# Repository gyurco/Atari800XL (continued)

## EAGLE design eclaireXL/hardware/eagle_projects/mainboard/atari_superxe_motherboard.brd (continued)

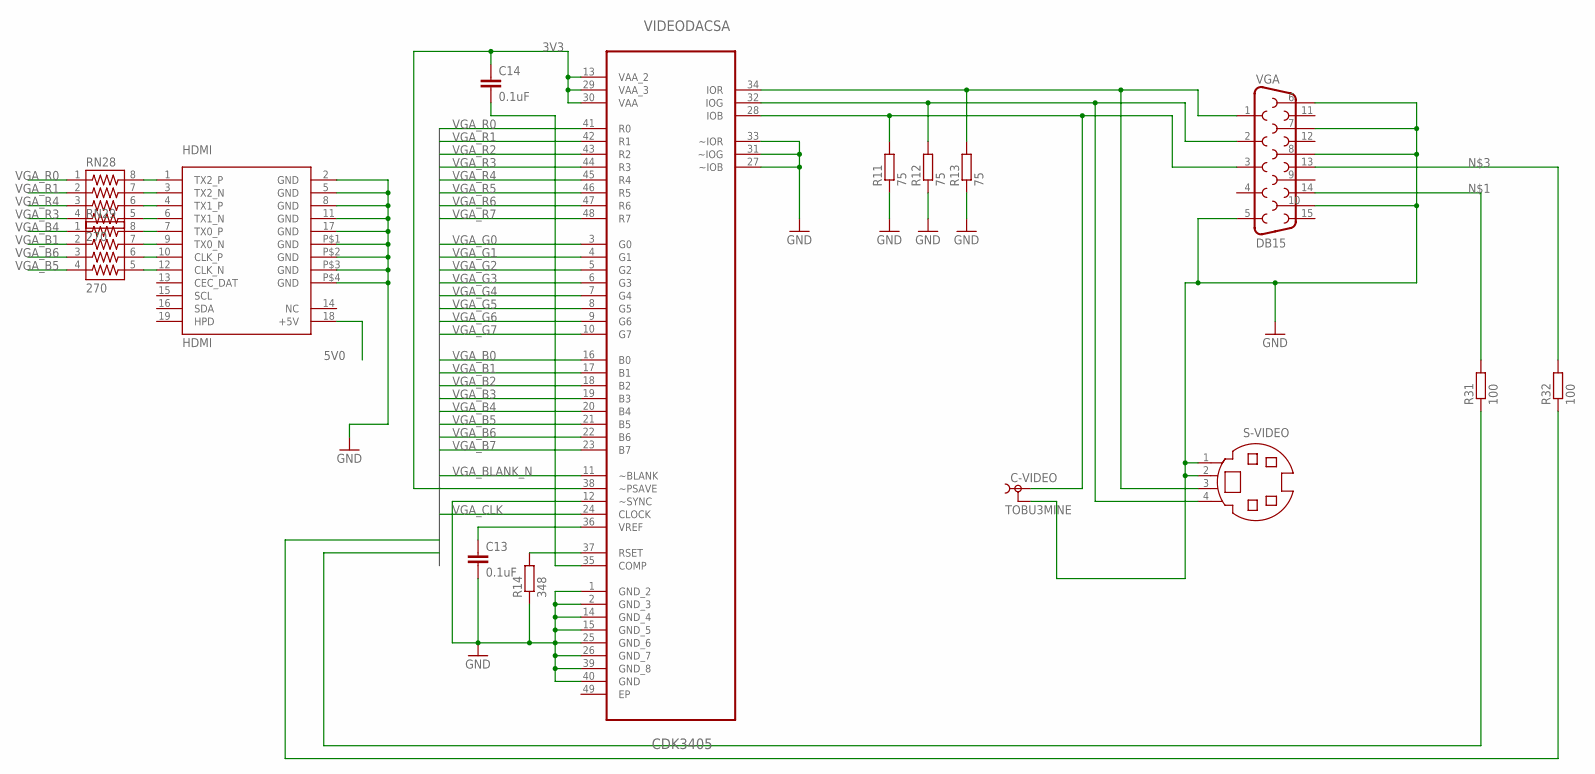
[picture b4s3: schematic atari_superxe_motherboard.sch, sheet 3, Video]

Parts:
C13, C14: 0.1uF; C0805
C-VIDEO: TOBU3MINE; TOBU3_EXT
HDMI: HDMI
R11, R12, R13: 75; M0805
R14: 348; M0805
R31, R32: 100; R0805
RN28, RN29: 270; 743-8
S-VIDEO: MD04SS; MDIN04SS
VGA: DB15
VIDEODACSA: CDK3405; QFP50P900X900X120-49N

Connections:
3V3: C14.1, VIDEODACSA.13 (VAA_2), VIDEODACSA.29 (VAA_3), VIDEODACSA.30 (VAA), VIDEODACSA.38 (~PSAVE); also elsewhere on the board
5V0: HDMI.18 (+5V); also elsewhere on the board
GND: C13.2, C-VIDEO.2, C-VIDEO.2@1 (2), C-VIDEO.2@2 (2), HDMI.2 (GND), HDMI.5 (GND), HDMI.8 (GND), HDMI.11 (GND), HDMI.17 (GND), HDMI.P$1 (GND), HDMI.P$2 (GND), HDMI.P$3 (GND), HDMI.P$4 (GND), R11.1, R12.1, R13.1, R14.1, S-VIDEO.1, S-VIDEO.2, VGA.5, VGA.6, VGA.7, VGA.8, VGA.10, VIDEODACSA.1 (GND_2), VIDEODACSA.2 (GND_3), VIDEODACSA.12 (~SYNC), VIDEODACSA.14 (GND_4), VIDEODACSA.15 (GND_5), VIDEODACSA.25 (GND_6), VIDEODACSA.26 (GND_7), VIDEODACSA.27 (~IOB), VIDEODACSA.31 (~IOG), VIDEODACSA.33 (~IOR), VIDEODACSA.39 (GND_8), VIDEODACSA.40 (GND); also elsewhere on the board
HSYNC: R32.1; also elsewhere on the board
unnamed: R31.2, VGA.14
unnamed: R32.2, VGA.13
unnamed: R13.2, S-VIDEO.3, VGA.1, VIDEODACSA.34 (IOR)
unnamed: R12.2, S-VIDEO.4, VGA.2, VIDEODACSA.32 (IOG)
unnamed: C13.1, VIDEODACSA.36 (VREF)
unnamed: R14.2, VIDEODACSA.37 (RSET)
unnamed: C14.2, VIDEODACSA.35 (COMP)
unnamed: HDMI.1 (TX2_P), RN28.8
unnamed: C-VIDEO.1, R11.2, VGA.3, VIDEODACSA.28 (IOB)
unnamed: HDMI.3 (TX2_N), RN28.7
unnamed: HDMI.4 (TX1_P), RN28.6
unnamed: HDMI.6 (TX1_N), RN28.5
unnamed: HDMI.7 (TX0_P), RN29.8
unnamed: HDMI.9 (TX0_N), RN29.7
unnamed: HDMI.10 (CLK_P), RN29.6
unnamed: HDMI.12 (CLK_N), RN29.5
VGA_B0: VIDEODACSA.16 (B0); also elsewhere on the board
VGA_B1: RN29.2, VIDEODACSA.17 (B1); also elsewhere on the board
VGA_B2: VIDEODACSA.18 (B2); also elsewhere on the board
VGA_B3: VIDEODACSA.19 (B3); also elsewhere on the board
VGA_B4: RN29.1, VIDEODACSA.20 (B4); also elsewhere on the board
VGA_B5: RN29.4, VIDEODACSA.21 (B5); also elsewhere on the board
VGA_B6: RN29.3, VIDEODACSA.22 (B6); also elsewhere on the board
VGA_B7: VIDEODACSA.23 (B7); also elsewhere on the board
VGA_BLANK_N: VIDEODACSA.11 (~BLANK); also elsewhere on the board
VGA_CLK: VIDEODACSA.24 (CLOCK); also elsewhere on the board
VGA_G0: VIDEODACSA.3 (G0); also elsewhere on the board
VGA_G1: VIDEODACSA.4 (G1); also elsewhere on the board
VGA_G2: VIDEODACSA.5 (G2); also elsewhere on the board
VGA_G3: VIDEODACSA.6 (G3); also elsewhere on the board
VGA_G4: VIDEODACSA.7 (G4); also elsewhere on the board
VGA_G5: VIDEODACSA.8 (G5); also elsewhere on the board
VGA_G6: VIDEODACSA.9 (G6); also elsewhere on the board
VGA_G7: VIDEODACSA.10 (G7); also elsewhere on the board
VGA_R0: RN28.1, VIDEODACSA.41 (R0); also elsewhere on the board
VGA_R1: RN28.2, VIDEODACSA.42 (R1); also elsewhere on the board
VGA_R2: VIDEODACSA.43 (R2); also elsewhere on the board
VGA_R3: RN28.4, VIDEODACSA.44 (R3); also elsewhere on the board
VGA_R4: RN28.3, VIDEODACSA.45 (R4); also elsewhere on the board
VGA_R5: VIDEODACSA.46 (R5); also elsewhere on the board
VGA_R6: VIDEODACSA.47 (R6); also elsewhere on the board
VGA_R7: VIDEODACSA.48 (R7); also elsewhere on the board
VSYNC: R31.1; also elsewhere on the board

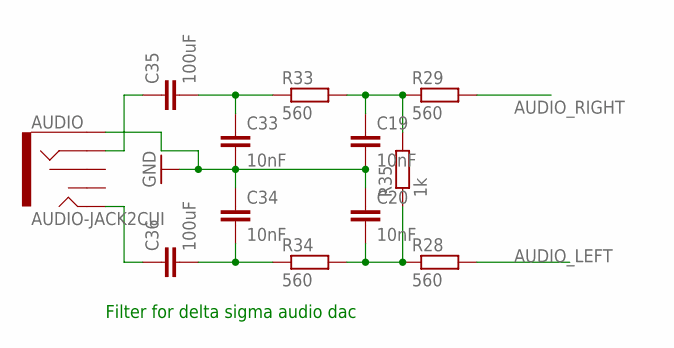
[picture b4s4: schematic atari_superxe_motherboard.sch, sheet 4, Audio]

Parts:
AUDIO: AUDIO-JACK2CUI; AUDIO-JACK-CUI-353X
C19, C20, C33, C34: 10nF; C0805
C35, C36: 100uF; C1206
R28, R29, R33, R34: 560; M0805
R35: 1k; M0805

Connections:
AUDIO_LEFT: R28.2; also elsewhere on the board
AUDIO_RIGHT: R29.2; also elsewhere on the board
GND: AUDIO.P$1 (SLEEVE), C19.2, C20.1, C33.2, C34.1; also elsewhere on the board
unnamed: C33.1, C35.2, R33.1
unnamed: C19.1, R29.1, R33.2, R35.2
unnamed: C20.2, R28.1, R34.2, R35.1
unnamed: AUDIO.P$3 (RING), C35.1
unnamed: AUDIO.P$2 (TIP), C36.1
unnamed: C34.2, C36.2, R34.1

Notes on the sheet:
Filter for delta sigma audio dac

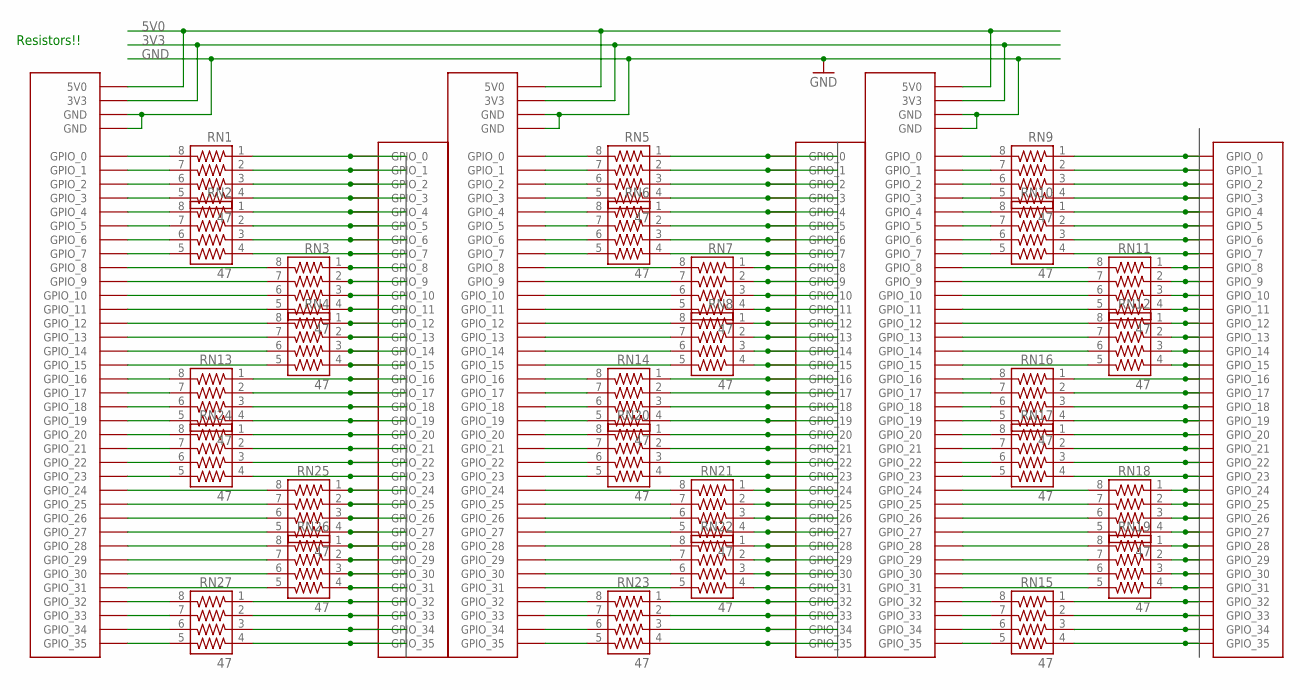
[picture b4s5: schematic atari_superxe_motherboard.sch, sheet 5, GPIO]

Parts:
GPIO_A: DE1_GPIO; DIL-100-2X20
GPIO_B: DE1_GPIO; DIL-100-2X20
GPIO_C: DE1_GPIO; DIL-100-2X20
RN1, RN2, RN3, RN4, RN5, RN6, RN7, RN8, RN9, RN10, RN11, RN12, RN13, RN14, RN15, RN16, RN17, RN18, RN19, RN20, RN21, RN22, RN23, RN24, RN25, RN26, RN27: 47; 743-8
U$3, U$4, U$5: HDR_SMALL_36_DEV_LALIGNED; HDR_141_36

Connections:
3V3: GPIO_A.29 (3V3), GPIO_B.29 (3V3), GPIO_C.29 (3V3); also elsewhere on the board
5V0: GPIO_A.11 (5V0), GPIO_B.11 (5V0), GPIO_C.11 (5V0); also elsewhere on the board
GND: GPIO_A.12 (GND), GPIO_A.30 (GND), GPIO_B.12 (GND), GPIO_B.30 (GND), GPIO_C.12 (GND), GPIO_C.30 (GND); also elsewhere on the board
GPIOA0: RN1.1, U$5.P$1 (GPIO_0); also elsewhere on the board
GPIOA1: RN1.2, U$5.P$2 (GPIO_1); also elsewhere on the board
GPIOA2: RN1.3, U$5.P$3 (GPIO_2); also elsewhere on the board
GPIOA3: RN1.4, U$5.P$4 (GPIO_3); also elsewhere on the board
GPIOA4: RN2.1, U$5.P$5 (GPIO_4); also elsewhere on the board
GPIOA5: RN2.2, U$5.P$6 (GPIO_5); also elsewhere on the board
GPIOA6: RN2.3, U$5.P$7 (GPIO_6); also elsewhere on the board
GPIOA7: RN2.4, U$5.P$8 (GPIO_7); also elsewhere on the board
GPIOA8: RN3.1, U$5.P$9 (GPIO_8); also elsewhere on the board
GPIOA9: RN3.2, U$5.P$10 (GPIO_9); also elsewhere on the board
GPIOA10: RN3.3, U$5.P$11 (GPIO_10); also elsewhere on the board
GPIOA11: RN3.4, U$5.P$12 (GPIO_11); also elsewhere on the board
GPIOA12: RN4.1, U$5.P$13 (GPIO_12); also elsewhere on the board
GPIOA13: RN4.2, U$5.P$14 (GPIO_13); also elsewhere on the board
GPIOA14: RN4.3, U$5.P$15 (GPIO_14); also elsewhere on the board
GPIOA15: RN4.4, U$5.P$16 (GPIO_15); also elsewhere on the board
GPIOA16: RN13.1, U$5.P$17 (GPIO_16); also elsewhere on the board
GPIOA17: RN13.2, U$5.P$18 (GPIO_17); also elsewhere on the board
GPIOA18: RN13.3, U$5.P$19 (GPIO_18); also elsewhere on the board
GPIOA19: RN13.4, U$5.P$20 (GPIO_19); also elsewhere on the board
GPIOA20: RN24.1, U$5.P$21 (GPIO_20); also elsewhere on the board
GPIOA21: RN24.2, U$5.P$22 (GPIO_21); also elsewhere on the board
GPIOA22: RN24.3, U$5.P$23 (GPIO_22); also elsewhere on the board
GPIOA23: RN24.4, U$5.P$24 (GPIO_23); also elsewhere on the board
GPIOA24: RN25.1, U$5.P$25 (GPIO_24); also elsewhere on the board
GPIOA25: RN25.2, U$5.P$26 (GPIO_25); also elsewhere on the board
GPIOA26: RN25.3, U$5.P$27 (GPIO_26); also elsewhere on the board
GPIOA27: RN25.4, U$5.P$28 (GPIO_27); also elsewhere on the board
GPIOA28: RN26.1, U$5.P$29 (GPIO_28); also elsewhere on the board
GPIOA29: RN26.2, U$5.P$30 (GPIO_29); also elsewhere on the board
GPIOA30: RN26.3, U$5.P$31 (GPIO_30); also elsewhere on the board
GPIOA31: RN26.4, U$5.P$32 (GPIO_31); also elsewhere on the board
GPIOA32: RN27.1, U$5.P$33 (GPIO_32); also elsewhere on the board
GPIOA33: RN27.2, U$5.P$34 (GPIO_33); also elsewhere on the board
GPIOA34: RN27.3, U$5.P$35 (GPIO_34); also elsewhere on the board
GPIOA35: RN27.4, U$5.P$36 (GPIO_35); also elsewhere on the board
GPIOB0: RN5.1, U$4.P$1 (GPIO_0); also elsewhere on the board
GPIOB1: RN5.2, U$4.P$2 (GPIO_1); also elsewhere on the board
GPIOB2: RN5.3, U$4.P$3 (GPIO_2); also elsewhere on the board
GPIOB3: RN5.4, U$4.P$4 (GPIO_3); also elsewhere on the board
GPIOB4: RN6.1, U$4.P$5 (GPIO_4); also elsewhere on the board
GPIOB5: RN6.2, U$4.P$6 (GPIO_5); also elsewhere on the board
GPIOB6: RN6.3, U$4.P$7 (GPIO_6); also elsewhere on the board
GPIOB7: RN6.4, U$4.P$8 (GPIO_7); also elsewhere on the board
GPIOB8: RN7.1, U$4.P$9 (GPIO_8); also elsewhere on the board
GPIOB9: RN7.2, U$4.P$10 (GPIO_9); also elsewhere on the board
GPIOB10: RN7.3, U$4.P$11 (GPIO_10); also elsewhere on the board
GPIOB11: RN7.4, U$4.P$12 (GPIO_11); also elsewhere on the board
GPIOB12: RN8.1, U$4.P$13 (GPIO_12); also elsewhere on the board
GPIOB13: RN8.2, U$4.P$14 (GPIO_13); also elsewhere on the board
GPIOB14: RN8.3, U$4.P$15 (GPIO_14); also elsewhere on the board
GPIOB15: RN8.4, U$4.P$16 (GPIO_15); also elsewhere on the board
GPIOB16: RN14.1, U$4.P$17 (GPIO_16); also elsewhere on the board
GPIOB17: RN14.2, U$4.P$18 (GPIO_17); also elsewhere on the board
GPIOB18: RN14.3, U$4.P$19 (GPIO_18); also elsewhere on the board
GPIOB19: RN14.4, U$4.P$20 (GPIO_19); also elsewhere on the board
GPIOB20: RN20.1, U$4.P$21 (GPIO_20); also elsewhere on the board
GPIOB21: RN20.2, U$4.P$22 (GPIO_21); also elsewhere on the board
GPIOB22: RN20.3, U$4.P$23 (GPIO_22); also elsewhere on the board
GPIOB23: RN20.4, U$4.P$24 (GPIO_23); also elsewhere on the board
GPIOB24: RN21.1, U$4.P$25 (GPIO_24); also elsewhere on the board
GPIOB25: RN21.2, U$4.P$26 (GPIO_25); also elsewhere on the board
GPIOB26: RN21.3, U$4.P$27 (GPIO_26); also elsewhere on the board
GPIOB27: RN21.4, U$4.P$28 (GPIO_27); also elsewhere on the board
GPIOB28: RN22.1, U$4.P$29 (GPIO_28); also elsewhere on the board
GPIOB29: RN22.2, U$4.P$30 (GPIO_29); also elsewhere on the board
GPIOB30: RN22.3, U$4.P$31 (GPIO_30); also elsewhere on the board
GPIOB31: RN22.4, U$4.P$32 (GPIO_31); also elsewhere on the board
GPIOB32: RN23.1, U$4.P$33 (GPIO_32); also elsewhere on the board
GPIOB33: RN23.2, U$4.P$34 (GPIO_33); also elsewhere on the board
GPIOB34: RN23.3, U$4.P$35 (GPIO_34); also elsewhere on the board
GPIOB35: RN23.4, U$4.P$36 (GPIO_35); also elsewhere on the board
GPIOC0: RN9.1, U$3.P$1 (GPIO_0); also elsewhere on the board
GPIOC1: RN9.2, U$3.P$2 (GPIO_1); also elsewhere on the board
GPIOC2: RN9.3, U$3.P$3 (GPIO_2); also elsewhere on the board
GPIOC3: RN9.4, U$3.P$4 (GPIO_3); also elsewhere on the board
GPIOC4: RN10.1, U$3.P$5 (GPIO_4); also elsewhere on the board
GPIOC5: RN10.2, U$3.P$6 (GPIO_5); also elsewhere on the board
GPIOC6: RN10.3, U$3.P$7 (GPIO_6); also elsewhere on the board
GPIOC7: RN10.4, U$3.P$8 (GPIO_7); also elsewhere on the board
GPIOC8: RN11.1, U$3.P$9 (GPIO_8); also elsewhere on the board
GPIOC9: RN11.2, U$3.P$10 (GPIO_9); also elsewhere on the board
GPIOC10: RN11.3, U$3.P$11 (GPIO_10); also elsewhere on the board
GPIOC11: RN11.4, U$3.P$12 (GPIO_11); also elsewhere on the board
GPIOC12: RN12.1, U$3.P$13 (GPIO_12); also elsewhere on the board
GPIOC13: RN12.2, U$3.P$14 (GPIO_13); also elsewhere on the board
GPIOC14: RN12.3, U$3.P$15 (GPIO_14); also elsewhere on the board
GPIOC15: RN12.4, U$3.P$16 (GPIO_15); also elsewhere on the board
GPIOC16: RN16.1, U$3.P$17 (GPIO_16); also elsewhere on the board
GPIOC17: RN16.2, U$3.P$18 (GPIO_17); also elsewhere on the board
GPIOC18: RN16.3, U$3.P$19 (GPIO_18); also elsewhere on the board
GPIOC19: RN16.4, U$3.P$20 (GPIO_19); also elsewhere on the board
GPIOC20: RN17.1, U$3.P$21 (GPIO_20); also elsewhere on the board
GPIOC21: RN17.2, U$3.P$22 (GPIO_21); also elsewhere on the board
GPIOC22: RN17.3, U$3.P$23 (GPIO_22); also elsewhere on the board
GPIOC23: RN17.4, U$3.P$24 (GPIO_23); also elsewhere on the board
GPIOC24: RN18.1, U$3.P$25 (GPIO_24); also elsewhere on the board
GPIOC25: RN18.2, U$3.P$26 (GPIO_25); also elsewhere on the board
GPIOC26: RN18.3, U$3.P$27 (GPIO_26); also elsewhere on the board
GPIOC27: RN18.4, U$3.P$28 (GPIO_27); also elsewhere on the board
GPIOC28: RN19.1, U$3.P$29 (GPIO_28); also elsewhere on the board
GPIOC29: RN19.2, U$3.P$30 (GPIO_29); also elsewhere on the board
GPIOC30: RN19.3, U$3.P$31 (GPIO_30); also elsewhere on the board
GPIOC31: RN19.4, U$3.P$32 (GPIO_31); also elsewhere on the board
GPIOC32: RN15.1, U$3.P$33 (GPIO_32); also elsewhere on the board
GPIOC33: RN15.2, U$3.P$34 (GPIO_33); also elsewhere on the board
GPIOC34: RN15.3, U$3.P$35 (GPIO_34); also elsewhere on the board
GPIOC35: RN15.4, U$3.P$36 (GPIO_35); also elsewhere on the board
unnamed: GPIO_C.1 (GPIO_0), RN9.8
unnamed: GPIO_A.1 (GPIO_0), RN1.8
unnamed: GPIO_A.2 (GPIO_1), RN1.7
unnamed: GPIO_A.3 (GPIO_2), RN1.6
unnamed: GPIO_A.4 (GPIO_3), RN1.5
unnamed: GPIO_A.5 (GPIO_4), RN2.8
unnamed: GPIO_A.6 (GPIO_5), RN2.7
unnamed: GPIO_A.7 (GPIO_6), RN2.6
unnamed: GPIO_A.8 (GPIO_7), RN2.5
unnamed: GPIO_A.9 (GPIO_8), RN3.8
unnamed: GPIO_A.10 (GPIO_9), RN3.7
unnamed: GPIO_A.13 (GPIO_10), RN3.6
unnamed: GPIO_A.14 (GPIO_11), RN3.5
unnamed: GPIO_A.15 (GPIO_12), RN4.8
unnamed: GPIO_A.17 (GPIO_14), RN4.6
unnamed: GPIO_A.16 (GPIO_13), RN4.7
unnamed: GPIO_A.18 (GPIO_15), RN4.5
unnamed: GPIO_A.19 (GPIO_16), RN13.8
unnamed: GPIO_A.20 (GPIO_17), RN13.7
unnamed: GPIO_A.21 (GPIO_18), RN13.6
unnamed: GPIO_A.22 (GPIO_19), RN13.5
unnamed: GPIO_A.23 (GPIO_20), RN24.8
unnamed: GPIO_A.25 (GPIO_22), RN24.6
unnamed: GPIO_A.24 (GPIO_21), RN24.7
unnamed: GPIO_A.26 (GPIO_23), RN24.5
unnamed: GPIO_A.27 (GPIO_24), RN25.8
unnamed: GPIO_A.28 (GPIO_25), RN25.7
unnamed: GPIO_A.31 (GPIO_26), RN25.6
unnamed: GPIO_A.32 (GPIO_27), RN25.5
unnamed: GPIO_A.33 (GPIO_28), RN26.8
unnamed: GPIO_A.34 (GPIO_29), RN26.7
unnamed: GPIO_A.35 (GPIO_30), RN26.6
unnamed: GPIO_A.36 (GPIO_31), RN26.5
unnamed: GPIO_A.37 (GPIO_32), RN27.8
unnamed: GPIO_A.38 (GPIO_33), RN27.7
unnamed: GPIO_A.39 (GPIO_34), RN27.6
unnamed: GPIO_A.40 (GPIO_35), RN27.5
unnamed: GPIO_B.1 (GPIO_0), RN5.8
unnamed: GPIO_B.2 (GPIO_1), RN5.7
unnamed: GPIO_B.3 (GPIO_2), RN5.6
unnamed: GPIO_B.4 (GPIO_3), RN5.5
unnamed: GPIO_B.5 (GPIO_4), RN6.8
unnamed: GPIO_B.6 (GPIO_5), RN6.7
unnamed: GPIO_B.7 (GPIO_6), RN6.6
unnamed: GPIO_B.8 (GPIO_7), RN6.5
unnamed: GPIO_B.9 (GPIO_8), RN7.8
unnamed: GPIO_B.10 (GPIO_9), RN7.7
unnamed: GPIO_B.13 (GPIO_10), RN7.6
unnamed: GPIO_B.14 (GPIO_11), RN7.5
unnamed: GPIO_B.15 (GPIO_12), RN8.8
unnamed: GPIO_B.16 (GPIO_13), RN8.7
unnamed: GPIO_B.17 (GPIO_14), RN8.6
unnamed: GPIO_B.18 (GPIO_15), RN8.5
unnamed: GPIO_B.19 (GPIO_16), RN14.8
unnamed: GPIO_B.20 (GPIO_17), RN14.7
unnamed: GPIO_B.21 (GPIO_18), RN14.6
unnamed: GPIO_B.22 (GPIO_19), RN14.5
unnamed: GPIO_B.23 (GPIO_20), RN20.8
unnamed: GPIO_B.24 (GPIO_21), RN20.7
unnamed: GPIO_B.25 (GPIO_22), RN20.6
unnamed: GPIO_B.26 (GPIO_23), RN20.5
unnamed: GPIO_B.27 (GPIO_24), RN21.8
unnamed: GPIO_B.28 (GPIO_25), RN21.7
unnamed: GPIO_B.31 (GPIO_26), RN21.6
unnamed: GPIO_B.32 (GPIO_27), RN21.5
unnamed: GPIO_B.33 (GPIO_28), RN22.8
unnamed: GPIO_B.34 (GPIO_29), RN22.7
unnamed: GPIO_B.35 (GPIO_30), RN22.6
unnamed: GPIO_B.36 (GPIO_31), RN22.5
unnamed: GPIO_B.37 (GPIO_32), RN23.8
unnamed: GPIO_B.38 (GPIO_33), RN23.7
unnamed: GPIO_B.39 (GPIO_34), RN23.6
unnamed: GPIO_B.40 (GPIO_35), RN23.5
unnamed: GPIO_C.2 (GPIO_1), RN9.7
unnamed: GPIO_C.3 (GPIO_2), RN9.6
unnamed: GPIO_C.4 (GPIO_3), RN9.5
unnamed: GPIO_C.5 (GPIO_4), RN10.8
unnamed: GPIO_C.6 (GPIO_5), RN10.7
unnamed: GPIO_C.7 (GPIO_6), RN10.6
unnamed: GPIO_C.8 (GPIO_7), RN10.5
unnamed: GPIO_C.9 (GPIO_8), RN11.8
unnamed: GPIO_C.10 (GPIO_9), RN11.7
unnamed: GPIO_C.13 (GPIO_10), RN11.6
unnamed: GPIO_C.14 (GPIO_11), RN11.5
unnamed: GPIO_C.15 (GPIO_12), RN12.8
unnamed: GPIO_C.16 (GPIO_13), RN12.7
unnamed: GPIO_C.17 (GPIO_14), RN12.6
unnamed: GPIO_C.18 (GPIO_15), RN12.5
unnamed: GPIO_C.19 (GPIO_16), RN16.8
unnamed: GPIO_C.20 (GPIO_17), RN16.7
unnamed: GPIO_C.21 (GPIO_18), RN16.6
unnamed: GPIO_C.22 (GPIO_19), RN16.5
unnamed: GPIO_C.23 (GPIO_20), RN17.8
unnamed: GPIO_C.24 (GPIO_21), RN17.7
unnamed: GPIO_C.25 (GPIO_22), RN17.6
unnamed: GPIO_C.26 (GPIO_23), RN17.5
unnamed: GPIO_C.27 (GPIO_24), RN18.8
unnamed: GPIO_C.28 (GPIO_25), RN18.7
unnamed: GPIO_C.31 (GPIO_26), RN18.6
unnamed: GPIO_C.32 (GPIO_27), RN18.5
unnamed: GPIO_C.33 (GPIO_28), RN19.8
unnamed: GPIO_C.34 (GPIO_29), RN19.7
unnamed: GPIO_C.35 (GPIO_30), RN19.6
unnamed: GPIO_C.36 (GPIO_31), RN19.5
unnamed: GPIO_C.37 (GPIO_32), RN15.8
unnamed: GPIO_C.38 (GPIO_33), RN15.7
unnamed: GPIO_C.39 (GPIO_34), RN15.6
unnamed: GPIO_C.40 (GPIO_35), RN15.5

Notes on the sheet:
Resistors!!

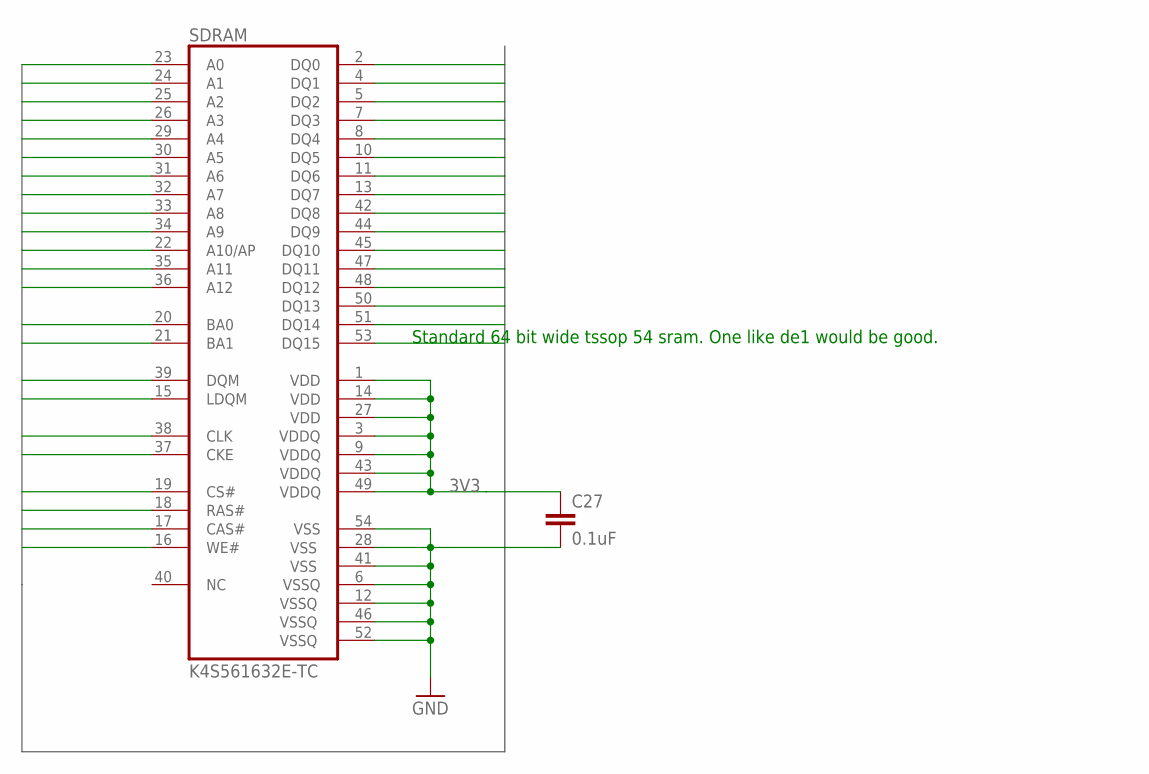
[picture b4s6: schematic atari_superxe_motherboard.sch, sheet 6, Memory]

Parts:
C27: 0.1uF; C0805
SDRAM: K4S561632E-TC; TSOP54

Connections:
3V3: C27.1, SDRAM.1 (VDD), SDRAM.3 (VDDQ), SDRAM.9 (VDDQ), SDRAM.14 (VDD), SDRAM.27 (VDD), SDRAM.43 (VDDQ), SDRAM.49 (VDDQ); also elsewhere on the board
A0: SDRAM.23 (A0); also elsewhere on the board
A1: SDRAM.24 (A1); also elsewhere on the board
A2: SDRAM.25 (A2); also elsewhere on the board
A3: SDRAM.26 (A3); also elsewhere on the board
A4: SDRAM.29 (A4); also elsewhere on the board
A5: SDRAM.30 (A5); also elsewhere on the board
A6: SDRAM.31 (A6); also elsewhere on the board
A7: SDRAM.32 (A7); also elsewhere on the board
A8: SDRAM.33 (A8); also elsewhere on the board
A9: SDRAM.34 (A9); also elsewhere on the board
A10: SDRAM.22 (A10/AP); also elsewhere on the board
A11: SDRAM.35 (A11); also elsewhere on the board
A12: SDRAM.36 (A12); also elsewhere on the board
BA0: SDRAM.20 (BA0); also elsewhere on the board
BA1: SDRAM.21 (BA1); also elsewhere on the board
CAS_N: SDRAM.17 (CAS#); also elsewhere on the board
CKE: SDRAM.37 (CKE); also elsewhere on the board
CS_N: SDRAM.19 (CS#); also elsewhere on the board
DQ0: SDRAM.2 (DQ0); also elsewhere on the board
DQ1: SDRAM.4 (DQ1); also elsewhere on the board
DQ2: SDRAM.5 (DQ2); also elsewhere on the board
DQ3: SDRAM.7 (DQ3); also elsewhere on the board
DQ4: SDRAM.8 (DQ4); also elsewhere on the board
DQ5: SDRAM.10 (DQ5); also elsewhere on the board
DQ6: SDRAM.11 (DQ6); also elsewhere on the board
DQ7: SDRAM.13 (DQ7); also elsewhere on the board
DQ8: SDRAM.42 (DQ8); also elsewhere on the board
DQ9: SDRAM.44 (DQ9); also elsewhere on the board
DQ10: SDRAM.45 (DQ10); also elsewhere on the board
DQ11: SDRAM.47 (DQ11); also elsewhere on the board
DQ12: SDRAM.48 (DQ12); also elsewhere on the board
DQ13: SDRAM.50 (DQ13); also elsewhere on the board
DQ14: SDRAM.51 (DQ14); also elsewhere on the board
DQ15: SDRAM.53 (DQ15); also elsewhere on the board
GND: C27.2, SDRAM.6 (VSSQ), SDRAM.12 (VSSQ), SDRAM.28 (VSS), SDRAM.41 (VSS), SDRAM.46 (VSSQ), SDRAM.52 (VSSQ), SDRAM.54 (VSS); also elsewhere on the board
RAS_N: SDRAM.18 (RAS#); also elsewhere on the board
SDRAM_CLK: SDRAM.38 (CLK); also elsewhere on the board
SDRAM_LDQM: SDRAM.15 (LDQM); also elsewhere on the board
SDRAM_UDQM: SDRAM.39 (DQM); also elsewhere on the board
WE_N: SDRAM.16 (WE#); also elsewhere on the board

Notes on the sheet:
Standard 64 bit wide tssop 54 sram. One like de1 would be good.

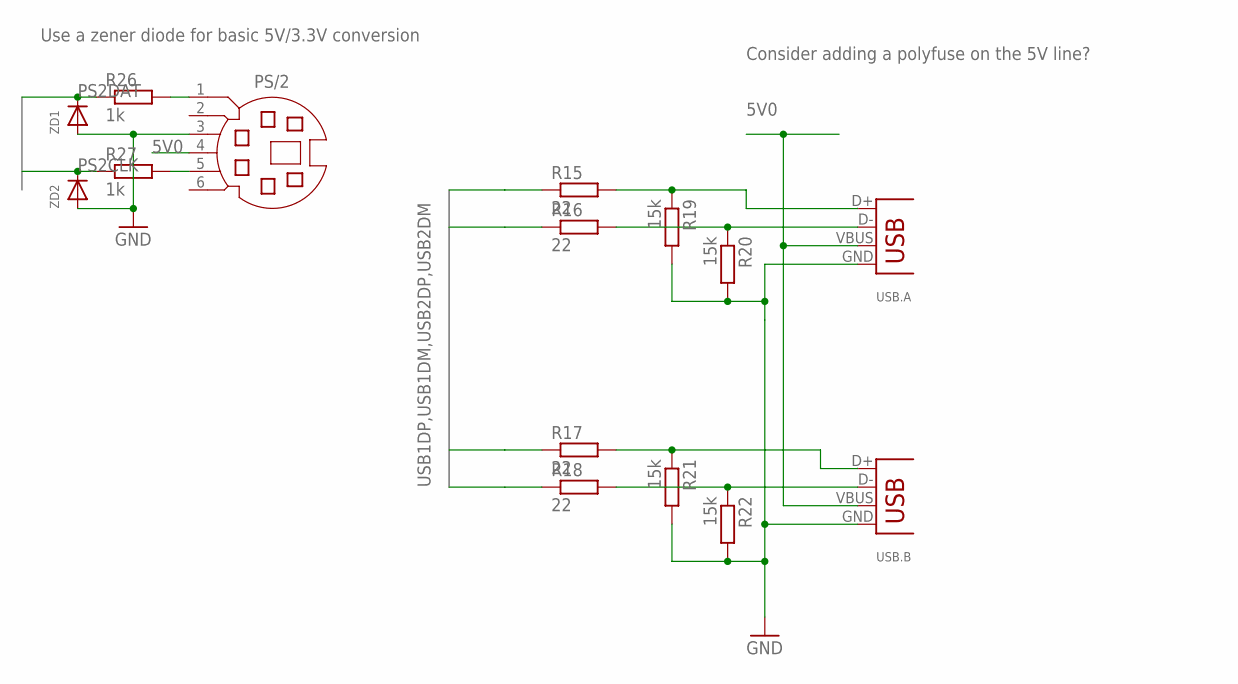
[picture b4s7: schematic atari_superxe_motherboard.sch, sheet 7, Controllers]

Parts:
PS/2: MD06SS; MDIN06SS
R15, R16, R17, R18: 22; R0805
R19, R20, R21, R22: 15k; R0805
R26, R27: 1k; R0805
USB.A, USB.B: USB-A-H
ZD1, ZD2: DIODESOT23_REFLOW; SOT23-R

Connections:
5V0: PS/2.4, USB.A.VBUS, USB.B.VBUS; also elsewhere on the board
GND: PS/2.3, R19.2, R20.2, R21.2, R22.2, USB.A.GND, USB.B.GND, ZD1.1 (A), ZD2.1 (A); also elsewhere on the board
unnamed: PS/2.5, R27.2
unnamed: R15.2, R19.1, USB.A.D+
unnamed: PS/2.1, R26.2
unnamed: R16.2, R20.1, USB.A.D-
unnamed: R17.2, R21.1, USB.B.D+
unnamed: R18.2, R22.1, USB.B.D-
PS2CLK: R27.1, ZD2.3 (C); also elsewhere on the board
PS2DAT: R26.1, ZD1.3 (C); also elsewhere on the board
USB1DM: R16.1; also elsewhere on the board
USB1DP: R15.1; also elsewhere on the board
USB2DM: R18.1; also elsewhere on the board
USB2DP: R17.1; also elsewhere on the board

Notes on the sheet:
Consider adding a polyfuse on the 5V line?
Use a zener diode for basic 5V/3.3V conversion

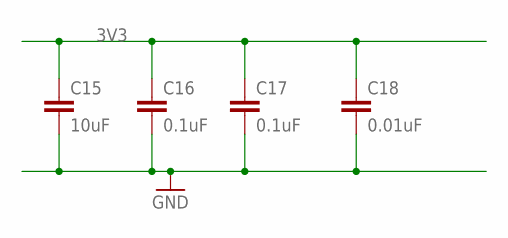
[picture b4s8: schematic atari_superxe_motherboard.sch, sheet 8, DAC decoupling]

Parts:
C15: 10uF; C0805
C16, C17: 0.1uF; C0805
C18: 0.01uF; C0805

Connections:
3V3: C15.1, C16.1, C17.1, C18.1; also elsewhere on the board
GND: C15.2, C16.2, C17.2, C18.2; also elsewhere on the board

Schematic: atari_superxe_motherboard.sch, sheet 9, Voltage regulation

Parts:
1.1V: 1.1V; SOT95P280X145-5N
2.5V: 2.5V; SOT95P280X145-5N
3.3/2.5/1.1/GND: PINHD-1X4; 1X04
3.3V: 3.3V; SOT95P280X145-5N
5V_IN: ZX62D-B-5P8
5V_IN_B: USB-B-H
C21, C22, C23, C31, C32: 10uF; C0805
C24, C25, C26: 22uF; C0805
C37: 15pF; C0805
L1, L2, L3: 1uH; L3225M
PF1: 1A; R1206
POWER_SW: 450302014072ROCKER2; ROCKER_VERT_SPDT2
R7: 4k7; R0805
R30: 1k; R0805
R36: 240; R0805
R37: 200; R0805

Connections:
1V1: 3.3/2.5/1.1/GND.3, C26.1, C37.1, L3.2, R36.2; also elsewhere on the board
2V5: 2.5V.4 (ADJ/BYP), 3.3/2.5/1.1/GND.2, C25.1, L2.2; also elsewhere on the board
3V3: 3.3/2.5/1.1/GND.1, 3.3V.4 (ADJ/BYP), C24.1, L1.2; also elsewhere on the board
5V0: 1.1V.1 (VIN), 2.5V.1 (VIN), 3.3V.1 (VIN), C21.1, C22.1, C23.1, POWER_SW.P$3 (3), R7.1, R30.1; also elsewhere on the board
5V0FAST: 1.1V.3 (EN), C31.1, R30.2
5V0SLOW: 2.5V.3 (EN), 3.3V.3 (EN), C32.2, R7.2
GND: 1.1V.2 (GND), 2.5V.2 (GND), 3.3/2.5/1.1/GND.4, 3.3V.2 (GND), 5V_IN.P$5 (5), 5V_IN_B.GND, C21.2, C22.2, C23.2, C24.2, C25.2, C26.2, C31.2, C32.1, R37.1; also elsewhere on the board
unnamed: 5V_IN.P$1 (1), 5V_IN_B.VBUS, PF1.1
unnamed: 1.1V.5 (VOUT), L3.1
unnamed: 2.5V.5 (VOUT), L2.1
unnamed: 3.3V.5 (VOUT), L1.1
unnamed: PF1.2, POWER_SW.P$2 (1)
unnamed: 1.1V.4 (ADJ/BYP), C37.2, R36.1, R37.2

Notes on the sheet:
TODO: RC delay calc

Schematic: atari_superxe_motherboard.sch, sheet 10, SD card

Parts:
R23, R24, R25: 47K; M0805
U$2: SDMMCHALFHEIGHT; HALFHEIGHTSD

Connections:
3V3: R23.2, R24.2, R25.2, U$2.4 (VDD); also elsewhere on the board
GND: U$2.3 (VSS1), U$2.6 (VSS2), U$2.GP (GND), U$2.GP3 (COMMON_SW); also elsewhere on the board
SD_CS: R25.1, U$2.1 (CS); also elsewhere on the board
SD_DAT1: U$2.8 (DAT1); also elsewhere on the board
SD_DAT2: U$2.9 (DAT2); also elsewhere on the board
SD_DETECT: U$2.CD (CARD_DETECT); also elsewhere on the board
SD_MISO: R23.1, U$2.7 (DATA_OUT); also elsewhere on the board
SD_MOSI: R24.1, U$2.2 (DATA_IN); also elsewhere on the board
SD_SCK: U$2.5 (SCLK); also elsewhere on the board
SD_WRITEPROTECT: U$2.WP (WRITE_PROTECT); also elsewhere on the board

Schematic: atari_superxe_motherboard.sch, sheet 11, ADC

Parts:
ADC: MCP3021; SOT95P280X145-5N
C39: 0.1uF; C0805
JP1: M02PTH; 1X02
R38, R39: 2k; M0805

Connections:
3V3: R38.2, R39.1; also elsewhere on the board
5V0: ADC.1 (VCC), C39.1; also elsewhere on the board
AUDIO_IN: ADC.3 (AIN), JP1.1
GND: ADC.2 (VSS), C39.2, JP1.2; also elsewhere on the board
SCL: ADC.5 (SCL), R39.2; also elsewhere on the board
SDA: ADC.4 (SDA), R38.1; also elsewhere on the board

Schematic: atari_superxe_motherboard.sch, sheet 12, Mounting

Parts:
H1, H2, H3, H4, H5, H6, H7: MOUNT-PAD-ROUND2.5; 2,5-PAD

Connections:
GND: H1.B2,8, H2.B2,8, H3.B2,8, H4.B2,8, H5.B2,8, H6.B2,8, H7.B2,8; also elsewhere on the board

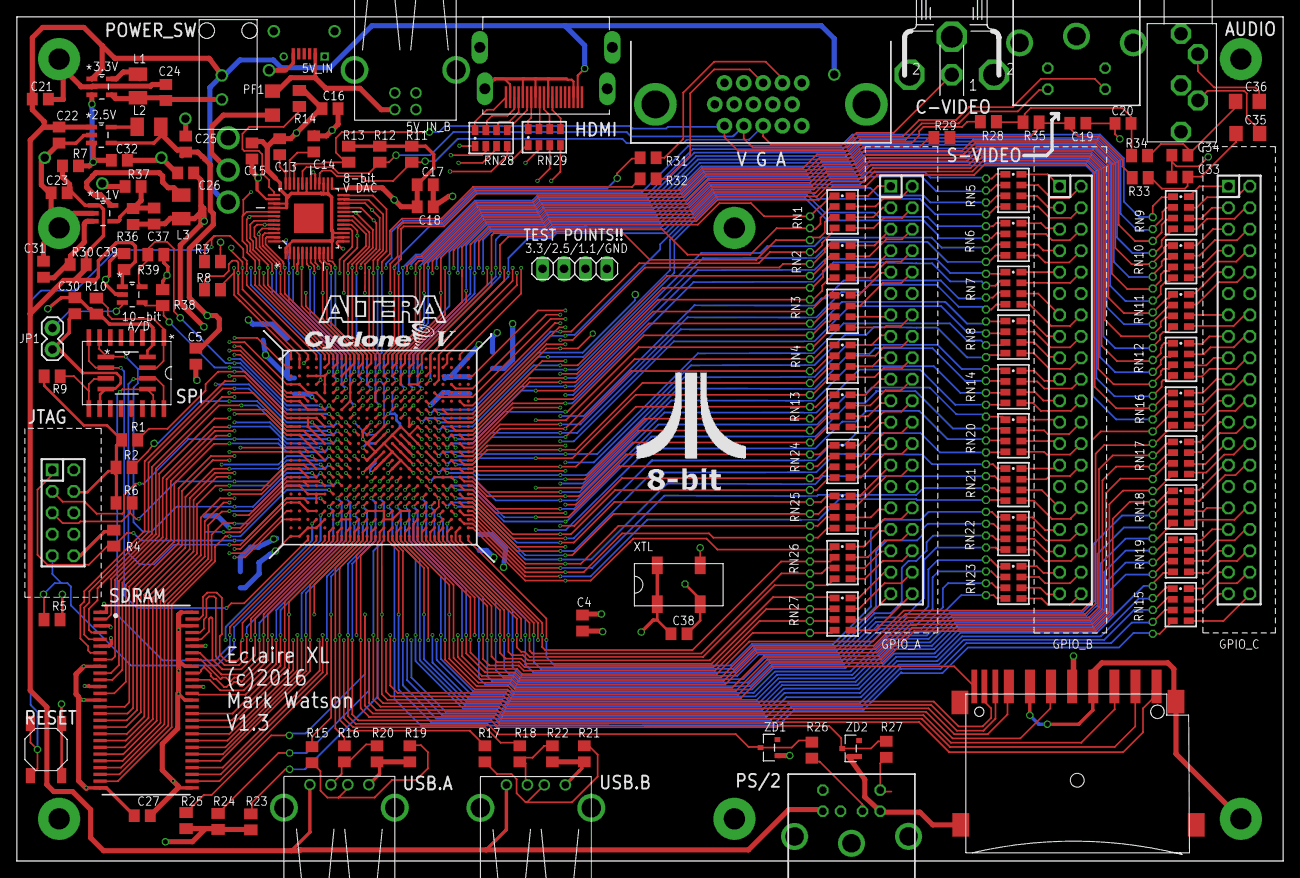
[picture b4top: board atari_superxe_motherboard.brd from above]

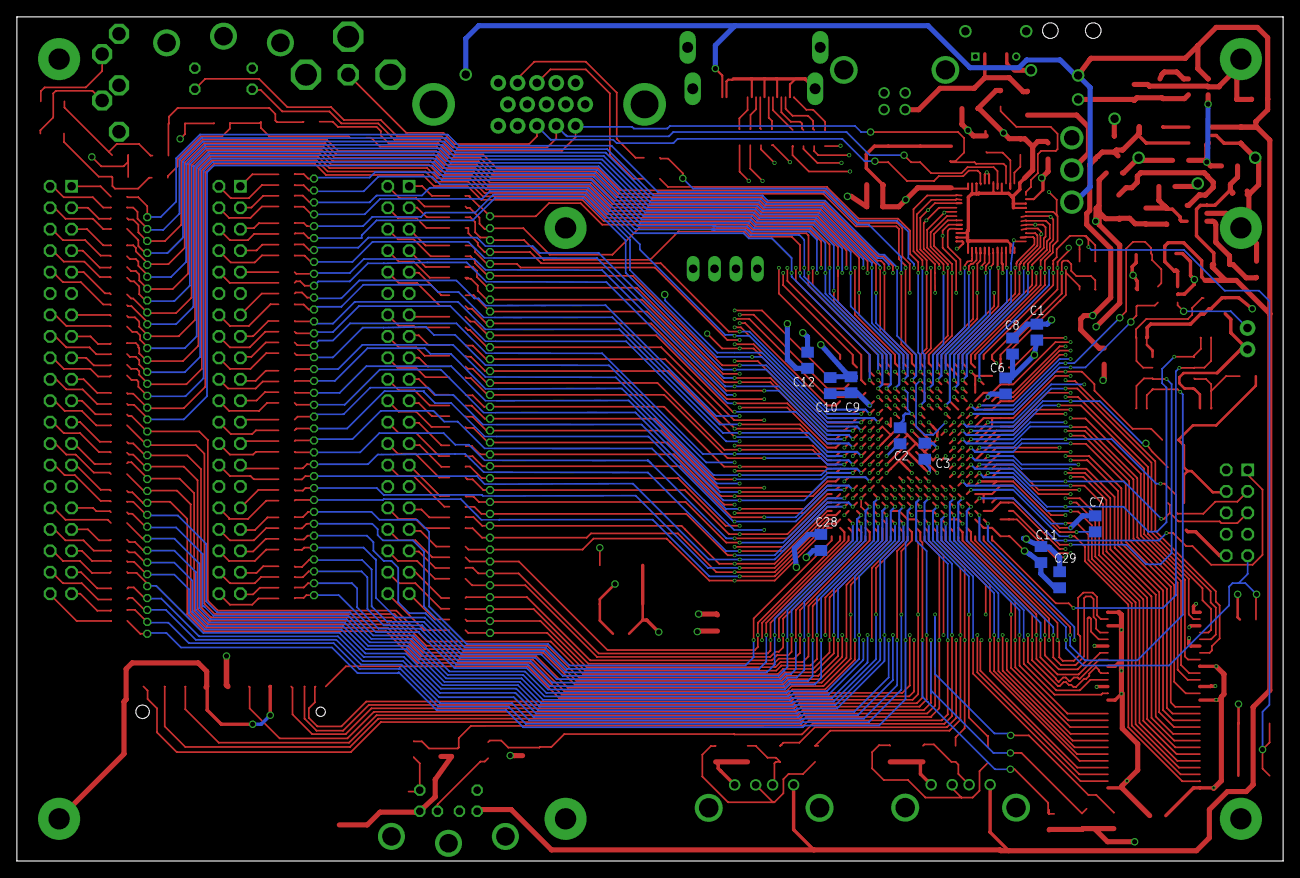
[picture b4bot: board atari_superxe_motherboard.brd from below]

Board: 4 copper layers, 150.0 x 100.0 mm, 151 parts (12 on the bottom side), 358 nets.
